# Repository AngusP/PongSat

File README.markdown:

<h3>PongSat Environment Sensing Datalogger</h3>

<h4>NOTICE: This isn't finished yet!!! I wouldn't try making one...</h4>

<p>The PongSat has a barometric pressure sensor, a humidity sensor, a temperature 
sensor and I2C bus for a 9DoF sensor stick (<a href=""http://www.sparkfun.com/products/10724">
SEN-10724</a>) which has on it an Accelerometer, Magnetometer and Gyroscope. The board
uses 3.3 volt logic and power.</p>

<p>This is a double sided PCB that will be able to fit inside a PingPong ball and 
so it can be used in JP Aeorspace's free Pongsat launches. All of the components are SMD, 
and so are pretty tiny, but can be harvested off a SparkFun OpenLog, and an Arduino Pro Micro 
(with the AtMega32u4).</p>

<p>Because of the 32u4 processor, this can be talked to and programmed via a USB Micro B 
connector, as commonly found on smartphone chargers. There is a I2C header with 3V3 and GND, 
but there is no FTDI or other serial connector other than the USB.</p>

<p>Because this is designed to fit in a pingpong ball, powering it can be difficult, so it 
is recommended to use two 3 volt coin cell batteries to get a total of 6 volts. The 
batteries should last a long time, but if you can find a small LiPo I'd strongly recommend 
using that.</p>

<p>None of these have ever been made in any way shape or form, so there is absolutely no 
guarantee of it being assemble-able, let alone functional. You do that at your own risk. 
After I have made on then I will say whether it works or not...</p>

<p>This project is in the public domain.</p>

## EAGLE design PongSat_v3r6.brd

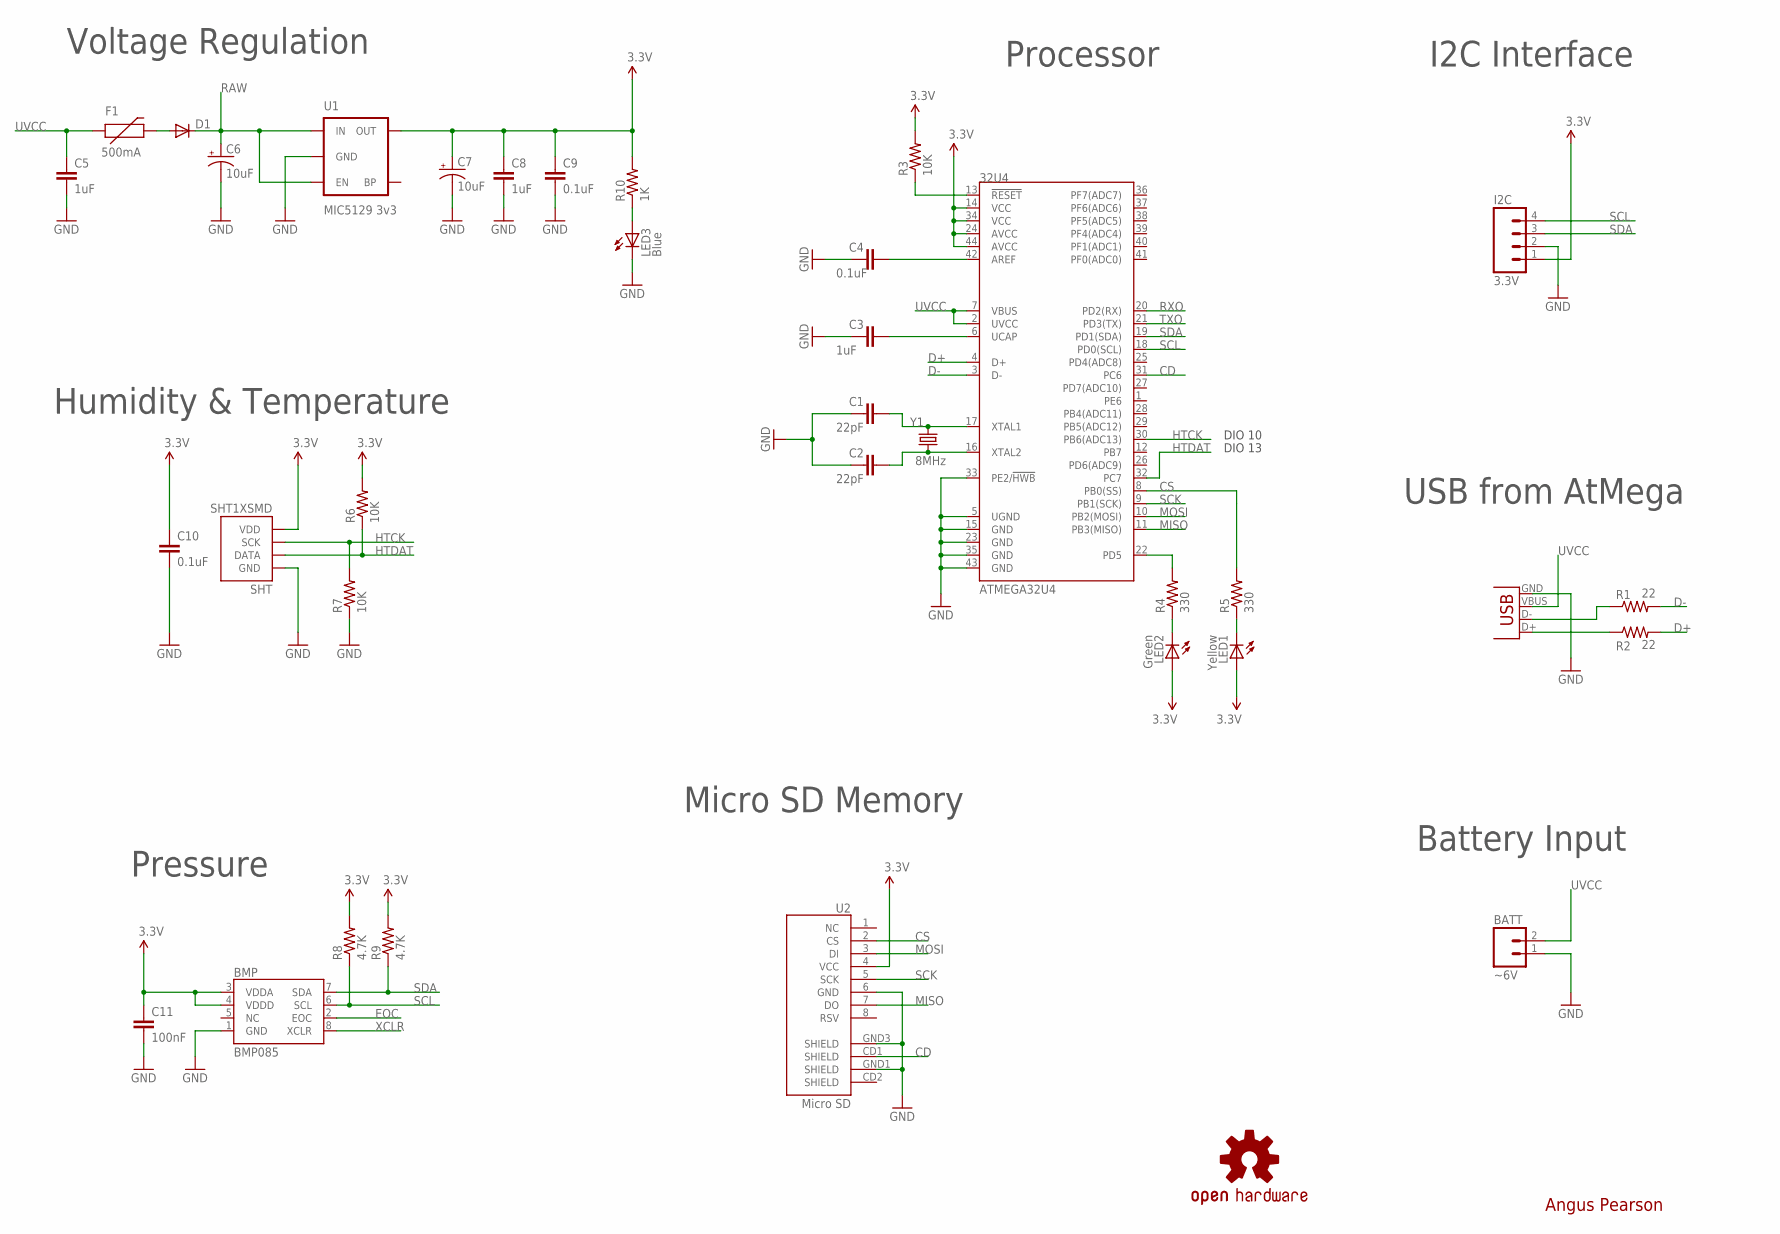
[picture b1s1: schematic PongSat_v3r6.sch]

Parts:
32U4: ATMEGA32U4; QFN-44-NOPAD
BATT: ~6V; 1X02
BMP: BMP085
C1, C2: 22pF; 0402-CAP
C3, C5, C8: 1uF; 0402-CAP
C4, C9, C10: 0.1uF; 0402-CAP
C6, C7: 10uF; EIA3216-KIT
C11: 100nF; 0402-CAP
D1: DIODESOT23; SOT23-3
F1: 500mA; 0603
I2C: 3.3V; 1X04
LED1: Yellow; LED-0603
LED2: Green; LED-0603
LED3: Blue; LED-0603
R1, R2: 22; 0402-RES
R3, R6, R7: 10K; 0402-RES
R4, R5: 330; 0402-RES
R8, R9: 4.7K; 0402-RES
R10: 1K; 0402-RES
SHT: SHT1XSMD; SHT1X
U1: MIC5129 3v3; SOT23-5
U2: Micro SD; MICRO-SD-SOCKET-PP
U$2: OSHW-LOGOS; OSHW-LOGO-S
X1: USB-MICROB
Y1: 8MHz; CRYSTAL-SMD-5X3

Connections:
3.3V: 32U4.14 (VCC), 32U4.24 (AVCC), 32U4.34 (VCC), 32U4.44 (AVCC), BMP.3 (VDDA), BMP.4 (VDDD), C7.A (+), C8.1, C9.1, C10.1, C11.1, I2C.1, LED1.A, LED2.A, R3.2, R6.2, R8.2, R9.2, R10.2, SHT.4 (VDD), U1.5 (OUT), U2.4 (VCC)
CD: 32U4.31 (PC6), U2.CD1 (SHIELD)
CS: 32U4.8 (PB0(SS)), R5.2, U2.2 (CS)
D+: 32U4.4 (D+), R2.2
D-: 32U4.3 (D-), R1.2
EOC: BMP.2 (EOC)
GND: 32U4.5 (UGND), 32U4.15 (GND), 32U4.23 (GND), 32U4.33 (PE2/!HWB), 32U4.35 (GND), 32U4.43 (GND), BATT.1, BMP.1 (GND), C1.1, C2.1, C3.1, C4.1, C5.2, C6.C (-), C7.C (-), C8.2, C9.2, C10.2, C11.2, I2C.2, LED3.C, R7.1, SHT.1 (GND), U1.2 (GND), U2.6 (GND), U2.GND1 (SHIELD), U2.GND3 (SHIELD), X1.GND
HTCK: 32U4.30 (PB6(ADC13)), R7.2, SHT.3 (SCK)
HTDAT: 32U4.32 (PC7), R6.1, SHT.2 (DATA)
MISO: 32U4.11 (PB3(MISO)), U2.7 (DO)
MOSI: 32U4.10 (PB2(MOSI)), U2.3 (DI)
unnamed: 32U4.16 (XTAL2), C2.2, Y1.1
unnamed: 32U4.17 (XTAL1), C1.2, Y1.3 (2)
unnamed: R1.1, X1.D-
unnamed: R2.1, X1.D+
unnamed: 32U4.6 (UCAP), C3.2
unnamed: LED2.C, R4.1
unnamed: LED1.C, R5.1
unnamed: LED3.A, R10.1
unnamed: 32U4.13 (!RESET), R3.1
unnamed: 32U4.42 (AREF), C4.2
unnamed: D1.1 (A), F1.2
RAW: C6.A (+), D1.3 (C), U1.1 (IN), U1.3 (EN)
RXO: 32U4.20 (PD2(RX))
SCK: 32U4.9 (PB1(SCK)), U2.5 (SCK)
SCL: 32U4.18 (PD0(SCL)), BMP.6 (SCL), I2C.4, R8.1
SDA: 32U4.19 (PD1(SDA)), BMP.7 (SDA), I2C.3, R9.1
TXLED: 32U4.22 (PD5), R4.2
TXO: 32U4.21 (PD3(TX))
UVCC: 32U4.2 (UVCC), 32U4.7 (VBUS), BATT.2, C5.1, F1.1, X1.VBUS
XCLR: BMP.8 (XCLR)

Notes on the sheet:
Angus Pearson
Voltage Regulation
Processor
Micro SD Memory
Pressure
Humidity & Temperature
I2C Interface
USB from AtMega
Battery Input
DIO 10
DIO 13

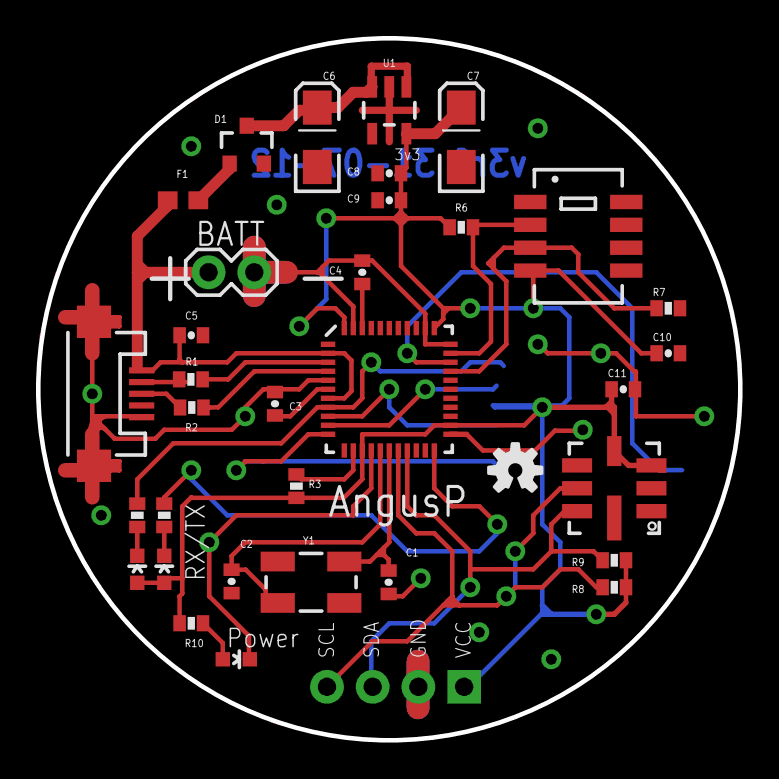
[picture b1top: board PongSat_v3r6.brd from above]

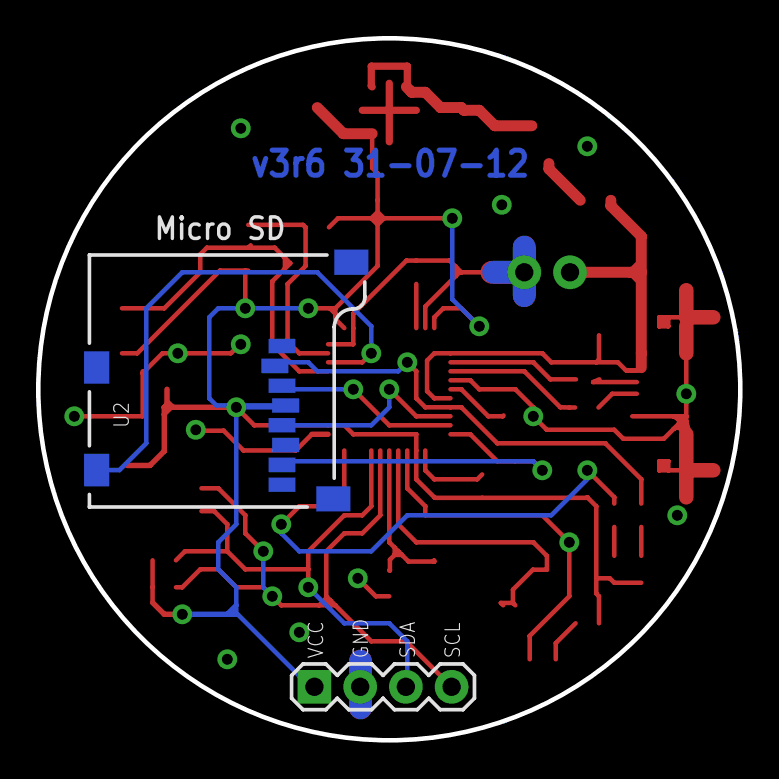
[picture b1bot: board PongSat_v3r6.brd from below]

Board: 2 copper layers, 39.0 x 39.0 mm, 36 parts (2 on the bottom side), 27 nets.

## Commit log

2012-07-28 Added v3 PCB
    Version 3 BETA (Vs 1 and 2 were alpha) PCB EAGLE files to repo. No
    Arduino code *yet*. Various Schematics from similar setups also added.
2012-07-28 Added Readme
2012-07-28 Added License
    WTFPL
2012-07-28 Updated PCB
    Completed PCB (V3 BETA) uploaded. PCB is now produceable, but not ERC'd
    or DRC'd.
2012-07-28 PCB Update
    Updated PCB with SD fix and also added new Schematics to repo.
2012-07-29 Updated PCB V3 Rev 3
    Updated PCB with new Silkscreen, improved routing and placement, bias
    and mounting holes. Included Schematics, PCB Printouts and Assembly
    diagrams in repo :-)
2012-07-29 Updated PCB and Gerbers
    Updated PCB with SilkScreen Fixes and also added Gerber Files to repo.
    Reorganised the directory structure to get data sheets and schematics
    out of the way. Also removed PCB versions 1 and 2 from repo.
2012-07-29 added .gitignore
2012-07-29 Updated R4 Gerbers
2012-07-29 Updated to Version 3 Revision 5
    I2C header is now PTH, and various other slight tweaks have been
    applied. New Gerber filed also committed. Directory structure also
    simplified and reorganised.
2012-07-29 Fixed .gitignore
2012-07-31 Revision 6
    Removed acid traps and improved silkscreen. New rev 6 gerber files as
    well. Version 4 will be along soon in the main branch…
2012-07-31 Gerber Compatibility Trace Width DRC fix
    Fixed issue where Batch PCB rejected Gerbers with capitalised
    extensions, and enlarged bottom copper version and date tracking that
    failed BatchPCB DRC on width. Added fixed CAM job based on SparkFun
    Gerber generator that does not capitalise extensions.
2012-09-03 Minor Fixes
2012-09-05 Added a Bill of Materials
2013-01-20 Changed License
    Went from WTFPL to Public Domain (No change in legal rights or
    obligations)

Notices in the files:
parts and their libraries:
SparkFun-DigitalIC: Licensing: CC v3.0 Share-Alike You are welcome to use this library for commercial purposes.
